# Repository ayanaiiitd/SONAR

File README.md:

SONAR-Sound Navigation and Ranging\n
Schematic and Board files of a transmitter and receiver are designed using EagleCAD.
Created a prototype of SONAR transmitter and receiver where Doppler shift was observed in the received signal from a moving metal target.
This design is used for tracking underwater submarines or finding objects beneath water.

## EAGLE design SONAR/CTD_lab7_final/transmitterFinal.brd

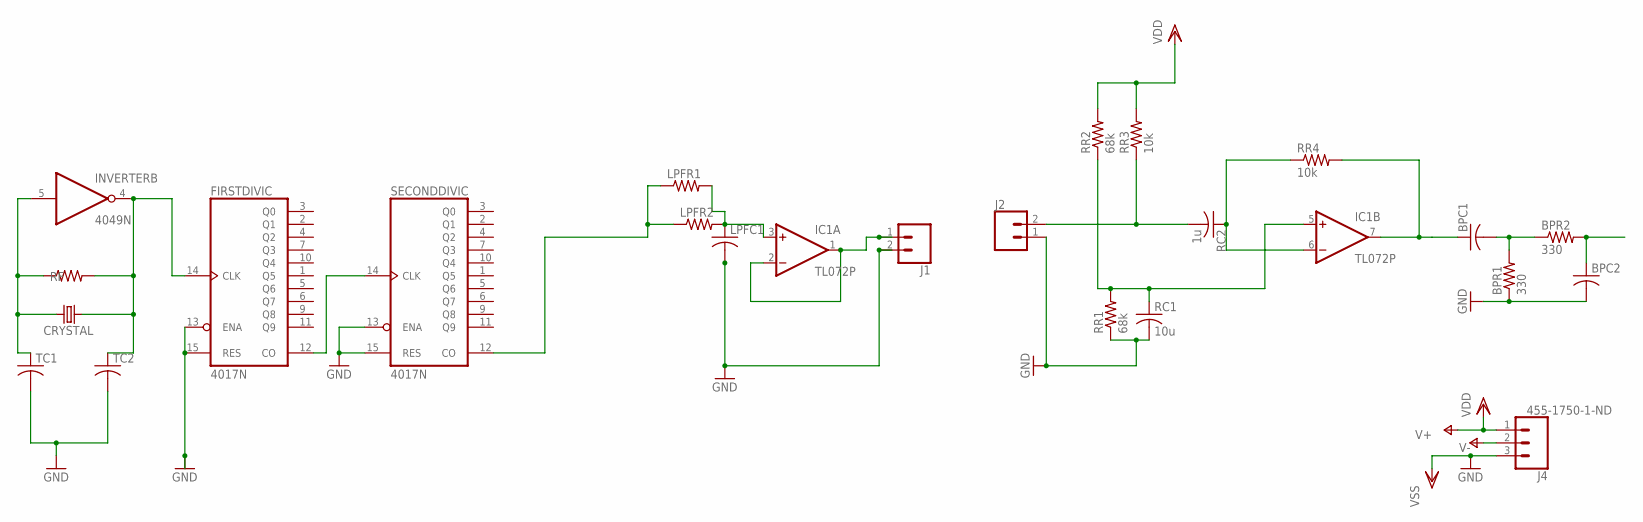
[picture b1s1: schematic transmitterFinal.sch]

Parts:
BPC1, BPC2: C-US050-025X075; C050-025X075
BPR1, BPR2: 330; 0309/12
CRYSTAL: CRYSTALHC49U-V; HC49U-V
FIRSTDIVIC: 4017N; DIL16
IC1: TL072P; DIL08
INVERTER: 4049N; DIL16
J1, J2: CONN_02; 1X02
J4: 455-1750-1-ND; 1X03
LPFC1: C-US050-025X075; C050-025X075
LPFR1, LPFR2: R-US_0309/12; 0309/12
RC1: 10u; C050-025X075
RC2: 1u; C050-025X075
RF: R-US_0411/15; 0411/15
RR1, RR2: 68k; 0309/12
RR3, RR4: 10k; 0309/12
SECONDDIVIC: 4017N; DIL16
TC1, TC2: C-US050-025X075; C050-025X075

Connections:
GND: BPC2.2, BPR1.1, FIRSTDIVIC.8 (VSS), FIRSTDIVIC.13 (ENA), FIRSTDIVIC.15 (RES), INVERTER.8 (VSS), J1.2, J2.1, J4.3, LPFC1.2, RC1.2, RR1.1, SECONDDIVIC.8 (VSS), SECONDDIVIC.13 (ENA), SECONDDIVIC.15 (RES), TC1.2, TC2.2
unnamed: CRYSTAL.2, FIRSTDIVIC.14 (CLK), INVERTER.4 (O), RF.2, TC2.1
unnamed: CRYSTAL.1, INVERTER.5 (I), RF.1, TC1.1
unnamed: FIRSTDIVIC.12 (CO), SECONDDIVIC.14 (CLK)
unnamed: LPFR1.1, LPFR2.1, SECONDDIVIC.12 (CO)
unnamed: J2.2, RC2.2, RR3.1
unnamed: IC1.3 (+IN), LPFC1.1, LPFR1.2, LPFR2.2
unnamed: IC1.1 (OUT), IC1.2 (-IN), J1.1
unnamed: IC1.5 (+IN), RC1.1, RR1.2, RR2.1
unnamed: BPC1.2, BPR1.2, BPR2.1
unnamed: IC1.6 (-IN), RC2.1, RR4.1
unnamed: BPC1.1, IC1.7 (OUT), RR4.2
unnamed: BPC2.1, BPR2.2
V-: IC1.4 (V-), J4.2
VDD: FIRSTDIVIC.16 (VDD), IC1.8 (V+), INVERTER.1 (VDD), J4.1, RR2.2, RR3.2, SECONDDIVIC.16 (VDD)

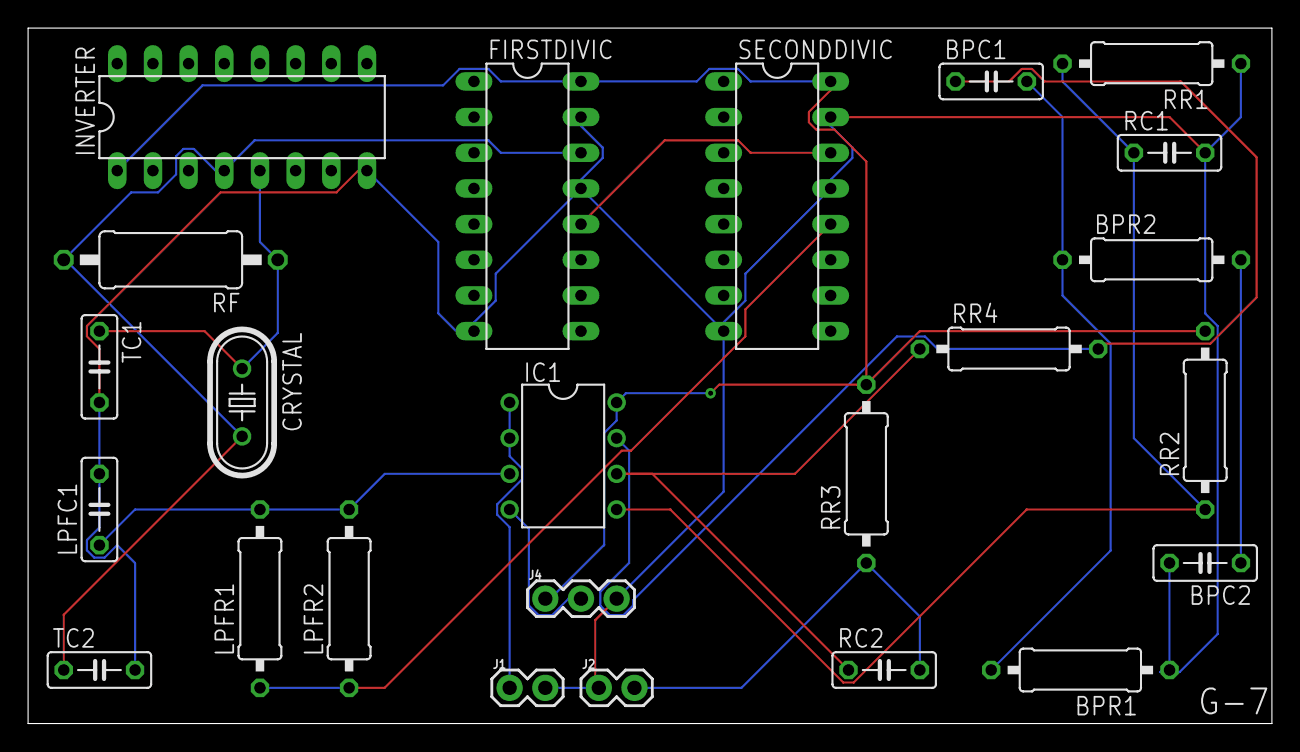
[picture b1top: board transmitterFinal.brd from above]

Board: 2 copper layers, 88.6 x 49.5 mm, 24 parts (0 on the bottom side), 15 nets.

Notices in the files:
parts and their libraries:
SparkFun-Connectors: Licensing: Creative Commons ShareAlike 4.0 International - https://creativecommons.org/licenses/by-sa/4.0
